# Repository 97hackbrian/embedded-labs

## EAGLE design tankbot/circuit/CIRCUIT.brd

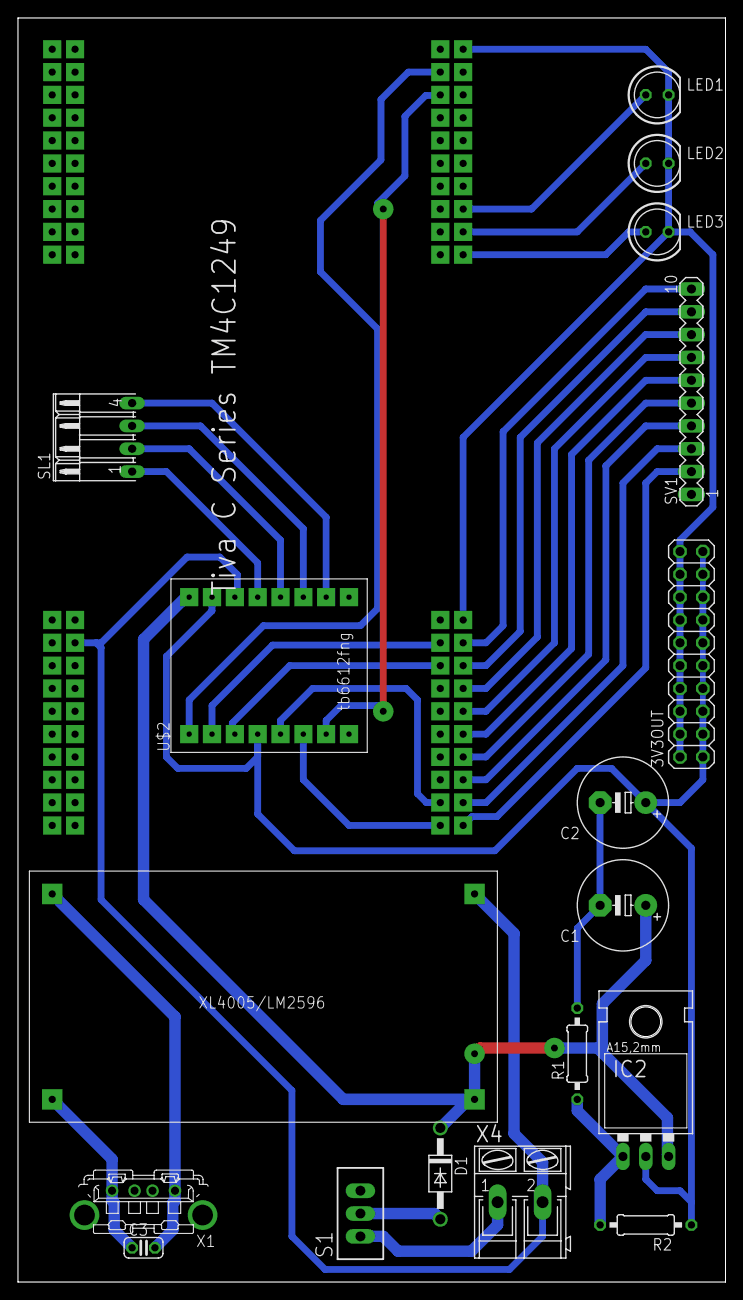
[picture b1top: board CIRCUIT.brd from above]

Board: 2 copper layers, 78.7 x 140.6 mm, 19 parts (1 on the bottom side), 31 nets.

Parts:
3V3OUT: 2X10
C1: 0.1u; E5-10,5
C2: 1u; E5-10,5
C3: 100u; C025-024X044
D1: 1N4004; DO41-10
IC2: 317TL
LED1, LED2, LED3: LED5MM
R1: 390; 0207/10
R2: 240; 0207/10
S1: TL36PO; TL3XPO
SL1: 04PA
SV1: MA10-1
U$1: TIVAEKTM4C; TIVAPINESPCB
U$2: TB6612FNGMODULE; TB6612FNG
U$3: STEPDOWN3A; REGULADORSTEP-DOWN3/5A
X1: KUSBVX
X4: AK300/2

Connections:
3V31A: 3V3OUT.1, 3V3OUT.3, 3V3OUT.5, 3V3OUT.7, 3V3OUT.9, 3V3OUT.11, 3V3OUT.13, 3V3OUT.15, 3V3OUT.17, 3V3OUT.19, C2.+, IC2.2, R2.1, U$2.P4, U$2.P15
5V3A: C3.1, U$3.P$3, X1.1
GND@1: 3V3OUT.2, 3V3OUT.4, 3V3OUT.6, 3V3OUT.8, 3V3OUT.10, 3V3OUT.12, 3V3OUT.14, 3V3OUT.16, 3V3OUT.18, 3V3OUT.20, LED1.K, LED2.K, LED3.K, U$1.P1, U$1.P21, U$1.P42, U$1.P62, U$2.P8, U$2.P9, U$2.P14, U$3.P$2, X4.2
GND@2: C3.2, U$3.P$4, X1.4
unnamed: S1.1, X4.1
unnamed: D1.A, S1.2
unnamed: IC2.1, R1.1, R2.2
unnamed: LED3.A, U$1.P10
unnamed: C1.-, C2.-, R1.2
unnamed: LED2.A, U$1.P9
unnamed: LED1.A, U$1.P8
unnamed: SV1.10, U$1.P22
unnamed: SL1.1, U$2.P13
unnamed: SL1.2, U$2.P12
unnamed: SL1.3, U$2.P11
unnamed: SL1.4, U$2.P10
unnamed: SV1.9, U$1.P23
unnamed: SV1.8, U$1.P24
unnamed: SV1.7, U$1.P25
unnamed: SV1.6, U$1.P26
unnamed: SV1.5, U$1.P27
unnamed: SV1.4, U$1.P28
unnamed: SV1.3, U$1.P29
unnamed: SV1.2, U$1.P30
PF2: U$1.P19, U$2.P1
PF3: U$1.P18, U$2.P7
PK4: U$1.P39, U$2.P2
PK5: U$1.P38, U$2.P3
PK6: U$1.P32, U$2.P5
PK7: U$1.P31, U$2.P6
VIN: C1.+, D1.C, IC2.3, U$2.P16, U$3.P$1

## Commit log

2023-08-05 ButtonWithoutHerencia
2023-08-05 ButtonsWithoutHerencia
2023-08-05 V05-BotoneSinAccion
2023-08-07 FailPushButton
2023-08-07 FailCountandPush
2023-08-07 requirements
2023-08-07 ositapull
2023-08-07 interfaz v1osita
2023-08-07 V1vaca
2023-08-07 V1-popup
2023-08-07 PopUpV2-winCorrect
2023-08-07 UIV1osita
2023-08-07 mergeUIV1-PopUpWindow
2023-08-08 UI-V2-fonts
2023-08-08 fail-Inpopup
2023-08-08 BeginPopup
2023-08-09 PopupV02
2023-08-09 CommitContinuePC
2023-08-10 Fail0count
2023-08-10 OsitaBebeTeAmo
2023-08-10 OsitaFuncionaV1
2023-08-10 Allv1
2023-08-10 AllFinalV1-5
2023-08-10 FinalV2
2023-08-10 FinalV1-5
2023-08-19 raspberryBegin
2023-08-19 Ej2Ej4
2023-08-20 Finish ej2ej4
2023-08-24 lab2complete
2023-08-26 tivaWare
2023-08-27 Lab3Gb
2023-08-31 Lab3Presentation
2023-09-12 lab5part1
2023-09-13 Lab5Finish
2023-09-13 RaspRevenge
2023-09-13 requirementsV2
2023-09-13 saveBlinky
2023-09-14 beforeExam
2023-09-14 examfail
2023-09-16 revengeV3
2023-09-21 exam
2023-09-28 lab4incomplete
2023-09-28 lad4Casi
2023-10-02 Lab4Complete
2023-10-12 lab6
2023-10-13 Lab6Complete
2023-10-19 incoplete
2023-10-19 fail
2023-10-19 ultimo
2023-10-23 Lab8init
2023-10-23 errorGit
2023-10-23 Image SemiComplete Co-authored-by: princessnymeria555 <princessnymeria555@users.noreply.github.com>
2023-10-26 UNirconAnterior
2023-10-26 Unir
2023-10-26 unirLAptop
2023-10-26 unir PC
2023-10-26 Semi Corrections
2023-10-26 with Decorators
2023-10-26 CancelSave Implementation
2023-10-26 multivideo
2023-10-26 arreglar camara
2023-10-26 ej6Incomplete
2023-10-26 EJE6complete
2023-10-26 eje7 incomplete
2023-10-26 ej7 incomplete
2023-10-29 DetectColorGood
2023-10-29 LAB8complete
2023-11-03 TivaFramework
2023-11-03 TivaWareFramework
2023-11-04 pcbV1
2023-11-04 PCBfinal
2023-11-06 reparar
2023-11-07 revisar
2023-11-07 probar
2023-11-07 dan los dos motores
2023-11-07 probado
2023-11-07 velocidad media
2023-11-07 motor controller
2023-11-07 da comand motor
2023-11-07 motorControllerComplete
2023-11-07 testMotorComplete
2023-11-07 DriverTivaPythonComplete
2023-11-07 TeleOpV1
2023-11-07 motores go
2023-11-07 ledsFUnciona
2023-11-07 tracking
2023-11-07 continuar track
2023-11-09 findFigures
2023-11-09 DETECION FUNCIONA
2023-11-09 on off control
2023-11-09 probar pid
2023-11-09 teleop2
2023-11-09 probar ex2
2023-11-09 probar ex 2
2023-11-09 bien
2023-11-09 semiComplete
2023-11-14 87.5
2023-11-15 lab9semi
2023-11-15 ej4lab9
2023-11-15 probar ej7
2023-11-16 velVideo
2023-11-16 Color
2023-11-16 MotorSeeker
2023-11-16 mejoras
2023-11-16 FINAL BOARD
2023-11-21 leds and mosfets
2023-11-21 motores apenas
2023-11-21 pwmgood
2023-11-21 Motores bien
2023-11-21 motors
2023-11-21 Timer4A
2023-11-21 Second motor example
2023-11-21 gripper
2023-11-23 MotorsGood
2023-11-23 lab10
2023-11-23 tivaUpdate
2023-11-23 compilado
2023-11-23 mosfetsON
2023-11-23 MosgOOD
2023-11-24 tivalibs
2023-12-10 basurero
